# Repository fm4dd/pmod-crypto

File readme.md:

## CRYPTO PMOD

### Description

This PMOD connects the Microchip ATECC508A  crypto authentication device over I2C, 
using Digilent's PMOD interface type 6A per PMOD specification v1.3.1. 
The PMOD module can be chained to add additional I2C devices to the bus. 
The onboard I2C bus pull-up resistors can be enabled/disabled, using the DIP switch.

http://fpga.fm4dd.com/

This design is registered under the OSHWA Open Source Hardware Self-Certification:

### Schematic

### PCB Gerber
[CRYPTO PMOD Gerber V1.0](20220624-crypto-gerber-v10.zip)

### PMOD Interface Pin Assignments

Pin  |	Label |	Description   | Pin  |	Label |	Description
-----|--------|---------------|------|--------|---------------
1    |	-     |	Not connected |7     | -      | Not connected
2    |	-     |	Not connected |8     | -      | Not connected
3    |	SCL   |	I2C clock     |9     | -      | Not connected
4    |  SDA   | I2C data      |10    | -      | Not connected
5    |  GND   | ground        |11    | GND    | ground
6    |  3V3   | 3.3V          |12    | 3V3    | 3.3V

All pins are passed through from connector J1 to J2, allowing to chain multiple type 6/6A PMODs.

### Example Operation

#### Linux / Raspberry Pi

Above shows the CRYPTO PMOD, connected to a [PMOD2RPI](https://github.com/fm4dd/pmod2rpi) interface board. When connected through the PMOD4 connector, the module can be controlled from the Raspberry Pi under Linux. Using i2cdetect, the ATECC508A IC responds under I2C bus address 0x60 (default).

```
pi@pi-ms05:~ $ i2cdetect 1
WARNING! This program can confuse your I2C bus, cause data loss and worse!
I will probe file /dev/i2c-1.
I will probe address range 0x08-0x77.
Continue? [Y/n]
     0  1  2  3  4  5  6  7  8  9  a  b  c  d  e  f
00:                         -- -- -- -- -- -- -- --
10: -- -- -- -- -- -- -- -- -- -- -- -- -- -- -- --
20: -- -- -- -- -- -- -- -- -- -- -- -- -- -- -- --
30: -- -- -- -- -- -- -- -- -- -- -- -- -- -- -- --
40: -- -- -- -- -- -- -- -- -- -- -- -- -- -- -- --
50: -- -- -- -- -- -- -- -- -- -- -- -- -- -- -- --
60: 60 -- -- -- -- -- -- -- -- -- -- -- -- -- -- --
70: -- -- -- -- -- -- -- --
```

To interact with the crypto IC under Linux, I am using "atecc-util", located at https://github.com/wirenboard/atecc-util.  This program is a frontend to the official Microchip library cryptoauthlib at https://github.com/MicrochipTech/cryptoauthlib.

Getting the client program:

```
pi@pi-ms05:~/atecc508a $ git clone https://github.com/wirenboard/atecc-util
Cloning into 'atecc-util'...
...
Receiving objects: 100% (351/351), 83.59 KiB | 2.88 MiB/s, done.
Resolving deltas: 100% (200/200), done.
```

Configure the I2C bus ID as 1, to match the RPI PMOD connection:

```
pi@pi-ms05:~/atecc508a/atecc-util $ vi config.h
#pragma once

#define DEFAULT_I2C_BUS 1
#define DEFAULT_I2C_SLAVE 0xC0

#define MAX_CMDS 32
```

Building the client program:

```
pi@pi-ms05:~/atecc508a $ cd atecc-util/
pi@pi-ms05:~/atecc508a/atecc-util $ git submodule init
pi@pi-ms05:~/atecc508a/atecc-util $ git submodule update
remote: Enumerating objects: 47, done.
remote: Counting objects: 100% (37/37), done.
remote: Total 47 (delta 36), reused 36 (delta 36), pack-reused 10
Unpacking objects: 100% (47/47), 12.65 KiB | 172.00 KiB/s, done.
From https://github.com/MicrochipTech/cryptoauthlib
 * branch              b976f640e4643a18876e0e5e600c8106f1bbe078 -> FETCH_HEAD
Submodule path 'cryptoauthlib': checked out 'b976f640e4643a18876e0e5e600c8106f1bbe078'
pi@pi-ms05:~/atecc508a/atecc-util $ make
...
```

Build result:

```
pi@pi-ms05:~/atecc508a/atecc-util $ ls -l ./atecc
-rwxr-xr-x 1 pi pi 439020 Jul  9 10:55 ./atecc
pi@pi-ms05:~/atecc508a/atecc-util $ ./atecc -h
atecc-util 0.4.7 (v0.4.7-dirty), build Jul  9 2022 10:54:59
Usage: ./atecc [-bshv] -c "cmd1 cmd1_args" [-c "cmd2 cmd2_args"]

        -b <i2c bus ID>
                I2C bus ID ATECC is connected to. Default is 9
        -s <i2c slave ID>
                I2C slave ID of ATECC. Default is 0xc0
        -c "cmd [arg1 [arg2 ...]]"
                Command and its arguments.
        -h[cmd_name]
                Print this help message or help message of specific command.
        -r <num_retries>
                Max number of retries for some commands. Default is 10
        -v      Print version and exit
```

Reading data from the crypto IC (factory-fresh  state):

```
pi@pi-ms05:~/atecc508a/atecc-util $ ./atecc -c 'info'
Found ATECC508A
pi@pi-ms05:~/atecc508a/atecc-util $ ./atecc -c 'serial'
0123**************
```

Below example dumps all configuration data (factory-fresh  state):

```
pi@pi-ms05:~/atecc508a/atecc-util $ ./atecc -c 'dump-config -'
============= Config zone dump: =============

000: 01         001: 23         002: 98         003: 3A
004: 00         005: 00         006: 50         007: 00
...
064: 00         065: 00         066: 00         067: 00
068: FF         069: FF         070: FF         071: FF
072: FF         073: FF         074: FF         075: FF
076: FF         077: FF         078: FF         079: FF
080: FF         081: FF         082: FF         083: FF
084: 00         085: 00         086: 55         087: 55
088: FF         089: FF         090: 00         091: 00
092: 00         093: 00         094: 00         095: 00
096: 33         097: 00         098: 33         099: 00
100: 33         101: 00         102: 1C         103: 00
104: 1C         105: 00         106: 1C         107: 00
108: 1C         109: 00         110: 1C         111: 00
112: 3C         113: 00         114: 3C         115: 00
116: 3C         117: 00         118: 3C         119: 00
120: 3C         121: 00         122: 3C         123: 00
124: 3C         125: 00         126: 1C         127: 00
===== Individual locks configuration ==
 Slot 00: unlocked
...
 Slot 15: unlocked

===== Slot configurations============
=========================  Slot: 0   ==================
Decoding SlotConfig value = 0x2083
Read key (except ECC private keys): 3
 If slot contains ECC private keys:
  External signatures of arbitrary messages are enabled: 1
  Internal signatures are enabled: 1
  ECDH operation is permitted for this key: 0
   ECDH master secret output mode: 0
NoMac bit: 0
LimitedUse bit: 0
EncryptRead bit: 0
IsSecret bit: 1
Write key: 0
Write config: 0x2 (hex) = 0010 (bin)
  Write cmd: Never
  DeriveKey cmd: Roll without MAC
  GenKey cmd: may be used
  PrivWrite cmd: Forbidden
-------------
Decoding KeyConfig value = 0x0033
Private bit: 1
PubInfo bit: 1
KeyType: 4 [P256]
Lockable bit: 1
ReqRandom bit: 0
ReqAuth bit: 0
AuthKey: 0
IntrusionDisable bit: 0
X509id: 0
...
=========================  Slot: 15   ==================
Decoding SlotConfig value = 0x8FAF
Read key (except ECC private keys): 15
 If slot contains ECC private keys:
  External signatures of arbitrary messages are enabled: 1
  Internal signatures are enabled: 1
  ECDH operation is permitted for this key: 1
   ECDH master secret output mode: 1
NoMac bit: 0
LimitedUse bit: 1
EncryptRead bit: 0
IsSecret bit: 1
Write key: 15
Write config: 0x8 (hex) = 1000 (bin)
  Write cmd: Never
  DeriveKey cmd: Can't be used
  GenKey cmd: may NOT be used
  PrivWrite cmd: Forbidden
-------------
Decoding KeyConfig value = 0x001C
Private bit: 0
PubInfo bit: 0
KeyType: 7 [SHA or other]
Lockable bit: 0
ReqRandom bit: 0
ReqAuth bit: 0
AuthKey: 0
IntrusionDisable bit: 0
X509id: 0
```

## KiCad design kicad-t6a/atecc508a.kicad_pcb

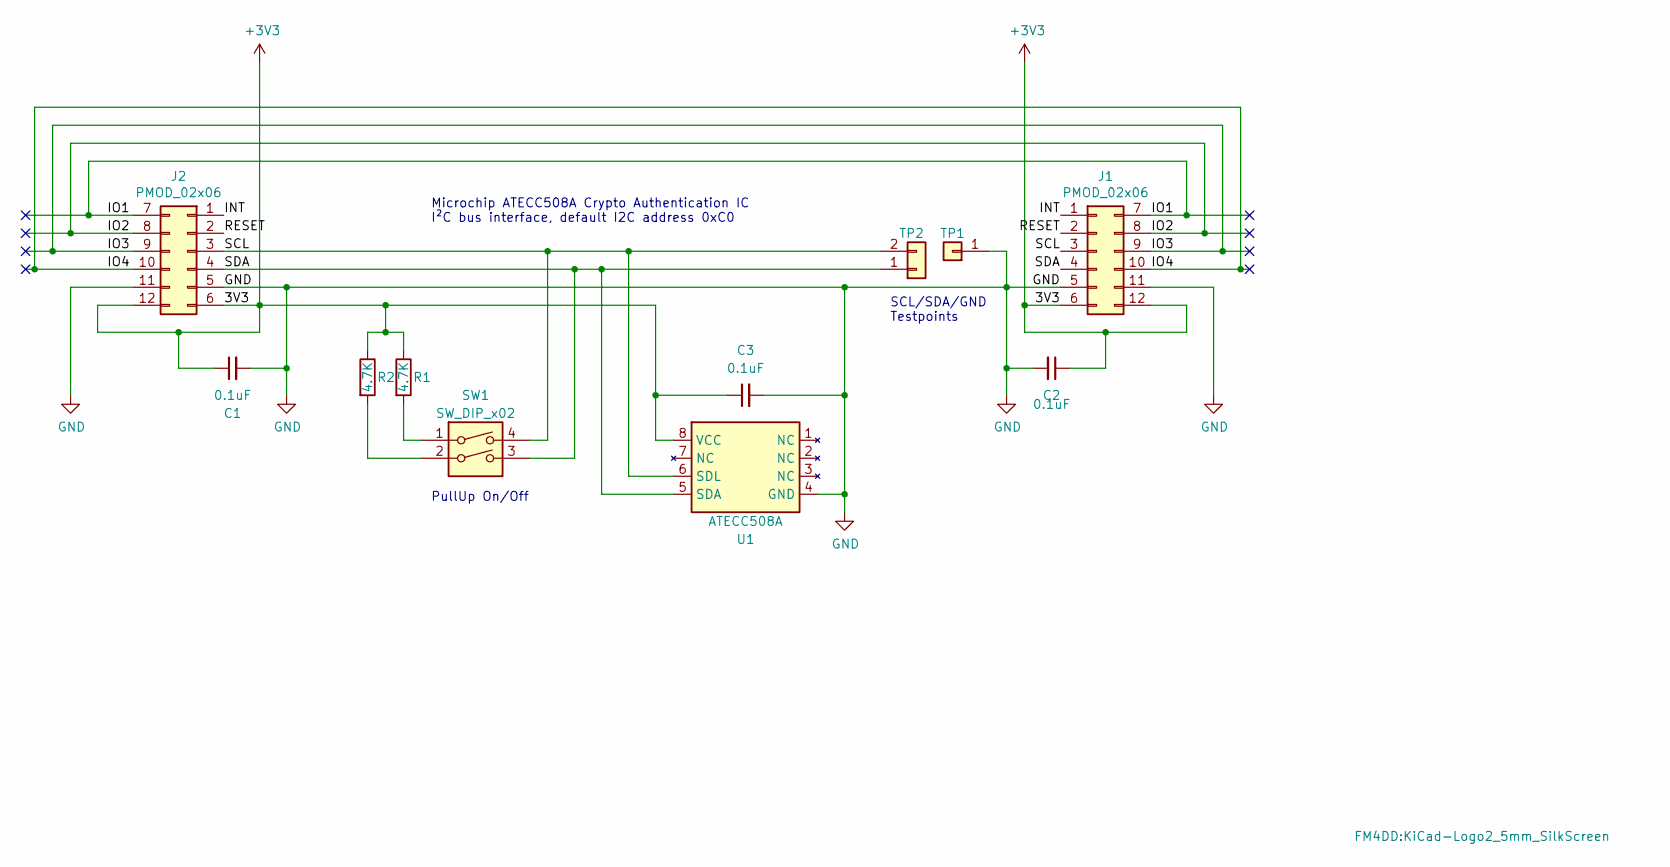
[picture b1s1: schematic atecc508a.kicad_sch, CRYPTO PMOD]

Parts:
C1, C2, C3: 0.1uF; C_0402_1005Metric
J1: PMOD_02x06; PMODPinSocket_2x06_P2.54mm_Horizontal
J2: PMOD_02x06; PMODHeader_2x06_P2.54mm_Horizontal
L1: Logo_KiCad_5mm; KiCad-Logo2_5mm_SilkScreen
R1, R2: 4.7K; R_0603_1608Metric
SW1: SW_DIP_x02; SW_DIP_SPSTx02_Slide_6.7x6.64mm_W7.62mm_P2.54mm_LowProfile
TP1: TestPoint_Conn_01x01; TestPoint_PinHeader_1x01_P2.54mm_Vertical
TP2: Conn_01x02; Testpoint_PinHeader_1x02_P2.54mm_Vertical
U1: ATECC508A; SOIC-8_3.9x4.9mm_P1.27mm

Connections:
+3V3: C1.1, C2.1, C3.1, J1.6, J1.12, J2.6, J2.12, R1.1, R2.1, U1.8 (VCC)
/INT: J1.1, J2.1
/IO1: J1.7, J2.7
/IO2: J1.8, J2.8
/IO3: J1.9, J2.9
/IO4: J1.10, J2.10
/RESET: J1.2, J2.2
/SCL: J1.3, J2.3, SW1.4, TP2.2, U1.6 (SDL)
/SDA: J1.4, J2.4, SW1.3, TP2.1, U1.5 (SDA)
GND: C1.2, C2.2, C3.2, J1.5, J1.11, J2.5, J2.11, TP1.1, U1.4 (GND)
unnamed: R1.2, SW1.1
unnamed: R2.2, SW1.2

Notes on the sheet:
SCL/SDA/GND Testpoints
PullUp On/Off
Microchip ATECC508A Crypto Authentication IC I²C bus interface, default I2C address 0xC0

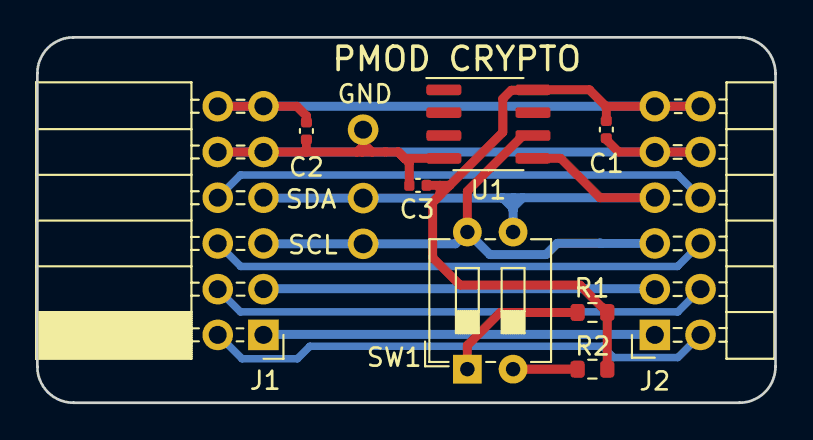
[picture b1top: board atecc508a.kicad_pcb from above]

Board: 2 copper layers, 41.0 x 20.3 mm, 13 parts (1 on the bottom side), 12 nets.

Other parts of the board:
Ref**: JLCPCB_Order_Number_Placeholder

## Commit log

2022-07-04 repo init
2022-07-09 update readme for linux
2022-07-18 add OSHW cert

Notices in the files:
kicad-t6a/atecc508a.kicad_pcb:
License: CC-BY-SA 4.0
